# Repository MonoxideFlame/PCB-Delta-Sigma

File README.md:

# Objective:

To design a second order PCB Delta sigma modulator (Takes a low bandwidth, high resolution signal, and converts it to a high bandwidth low resolution signal. ).

It simulates in LT SPICE providing an output of 70dB SNR, at a 2KHz Bandwidth. 

In Lab it tests similarly, though I haven't been able to create a good testing environment for it. 

# Motivation:

This was originally developed with a single ended op-amp in mind, however, I wanted much better Power supply rejection. It was too difficult to measure the performance. 

Now, it has been made more robust with a fully differential mode output. It also helps with signal a  integrity issues. I also added an LDO to keep the noise as minimal as possible. 

As a PCB level design, there are issues when it comes to what one can hope to achieve. Sigma Delta converters see a lot of use at the Die level because it is easier to use a low amount of power,
and keep noise levels equally low. Longer traces, with more capacitance and singal integrity issues mean that I will never be able to achieve the resolution and bandwidth product that the typical 
Sigma Delta Converter will achieve. 

This was mostly a didactic project. Undertaken to familiarize myself with board level design paradigms. 

# Contributors:

Mentor: Dr. William Paul Swartz.

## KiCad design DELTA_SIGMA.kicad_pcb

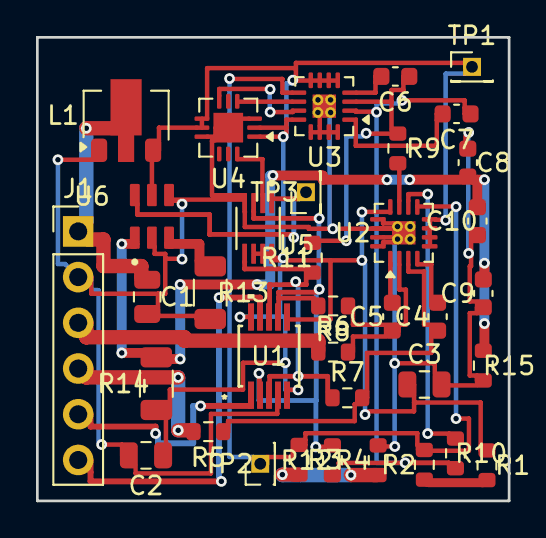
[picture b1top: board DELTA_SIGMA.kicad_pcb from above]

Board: 2 copper layers, 26.2 x 25.8 mm, 36 parts (0 on the bottom side), 28 nets.

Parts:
C1: C1; C_0805_2012Metric
C2: C2; C_0805_2012Metric
C3: C3; C_0805_2012Metric
C4: C4; C_0603_1608Metric
C5: C5; C_0603_1608Metric
C6: C6; C_0603_1608Metric
C7: C7; C_0603_1608Metric
C8: C8; C_0603_1608Metric
C9: C9; C_0603_1608Metric
C10: C10; C_0603_1608Metric
J1: J1; PinHeader_1x06_P2.54mm_Vertical
L1: L1; SOT-89-3
R1: R1; R_0603_1608Metric
R2: R2; R_0603_1608Metric
R3: R3; R_0603_1608Metric
R4: R4; R_0603_1608Metric
R5: R5; R_0603_1608Metric
R6: R6; R_0603_1608Metric
R7: R7; R_0603_1608Metric
R8: R8; R_0603_1608Metric
R9: R9; R_0603_1608Metric
R10: R10; R_0603_1608Metric
R11: R11; R_0603_1608Metric
R12: R12; R_0603_1608Metric
R13: R13; R_1206_3216Metric
R14: R14; R_1206_3216Metric
R15: R15; R_0603_1608Metric
TP1: TP1; PinHeader_1x01_P1.27mm_Vertical
TP2: TP2; PinHeader_1x01_P1.27mm_Vertical
TP3: TP3; PinHeader_1x01_P1.27mm_Vertical
U1: U1; RM_10_ADI
U2: U2; LFCSP-16-1EP_3x3mm_P0.5mm_EP1.3x1.3mm_ThermalVias
U3: U3; LFCSP-16-1EP_3x3mm_P0.5mm_EP1.3x1.3mm_ThermalVias
U4: U4; QFN-12-1EP_3x3mm_P0.5mm_EP1.65x1.65mm
U5: U5; SOP50P310X90-8N
U6: U6; SOT95P280X100-6N

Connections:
1V2: R2.2, R3.1, TP2.1, U2.9 (VOCM), U3.9 (VOCM)
3V3: C2.1, C3.1, L1.3 (VOUT), R1.1, R14.1, TP1.1, U1.5 (*DISABLE1), U1.6 (*DISABLE2), U1.10 (VS+), U2.5 (+Vs), U2.6 (+Vs), U2.7 (+Vs), U2.8 (+Vs), U2.12 (~(DISABLE)), U3.5 (+Vs), U3.6 (+Vs), U3.7 (+Vs), U3.8 (+Vs), U3.12 (~(DISABLE)), U4.1 (VDD), U4.2 (VCC), U4.7 (~(SHDN)), U4.8 (~(LE)), U5.6 (~(CLR)), U5.7 (~(PRE)), U5.8 (VCC), U6.5 (V+)
5V: C1.1, J1.1, L1.2 (VIN)
D+: R7.1, R11.1, U1.3 (IN1+), U1.8 (IN2-), U5.5 (Q)
D-: R8.2, R12.2, U1.2 (IN1-), U1.7 (IN2+), U5.3 (~(Q))
GND: C1.2, C2.2, C3.2, C8.1, C9.1, C10.1, J1.2, L1.1 (GND), R4.2, R13.2, R15.2, U1.4 (VS-), U2.13 (-Vs), U2.14 (-Vs), U2.15 (-Vs), U2.16 (-Vs), U2.17 (EP), U3.13 (-Vs), U3.14 (-Vs), U3.15 (-Vs), U3.16 (-Vs), U3.17 (EP), U4.3 (VEE), U4.9 (VEE), U4.13 (VEE), U5.4 (GND), U6.2 (GND), U6.4 (DIV)
unnamed: J1.5, U1.1 (OUT1)
unnamed: J1.6, U1.9 (OUT2)
unnamed: R1.2, R2.1
unnamed: R3.2, R4.1
unnamed: C4.2, U2.4 (+FB)
unnamed: C5.1, R6.2, R8.1, U2.2 (+IN)
unnamed: R10.1, U2.10 (+OUT)
unnamed: C5.2, U2.1 (-FB)
unnamed: C4.1, R5.1, R7.2, U2.3 (-IN)
unnamed: R9.2, U2.11 (-OUT)
unnamed: C6.2, U3.4 (+FB)
unnamed: C7.1, R10.2, R12.1, U3.2 (+IN)
unnamed: U3.10 (+OUT), U4.4 (+)
unnamed: C7.2, U3.1 (-FB)
unnamed: C6.1, R9.1, R11.2, U3.3 (-IN)
unnamed: U3.11 (-OUT), U4.6 (-)
unnamed: U4.12 (Q), U5.2 (D)
unnamed: TP3.1, U5.1 (CLK), U6.6 (OUT)
unnamed: C8.2, C9.2, C10.2, R14.2, R15.1, U6.1 (MOD)
unnamed: R13.1, U6.3 (SET)
Vin+: J1.3, R6.1
Vin-: J1.4, R5.2
